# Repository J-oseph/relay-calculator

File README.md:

# relay-calculator
Calculator made from electro-mechanical relays.

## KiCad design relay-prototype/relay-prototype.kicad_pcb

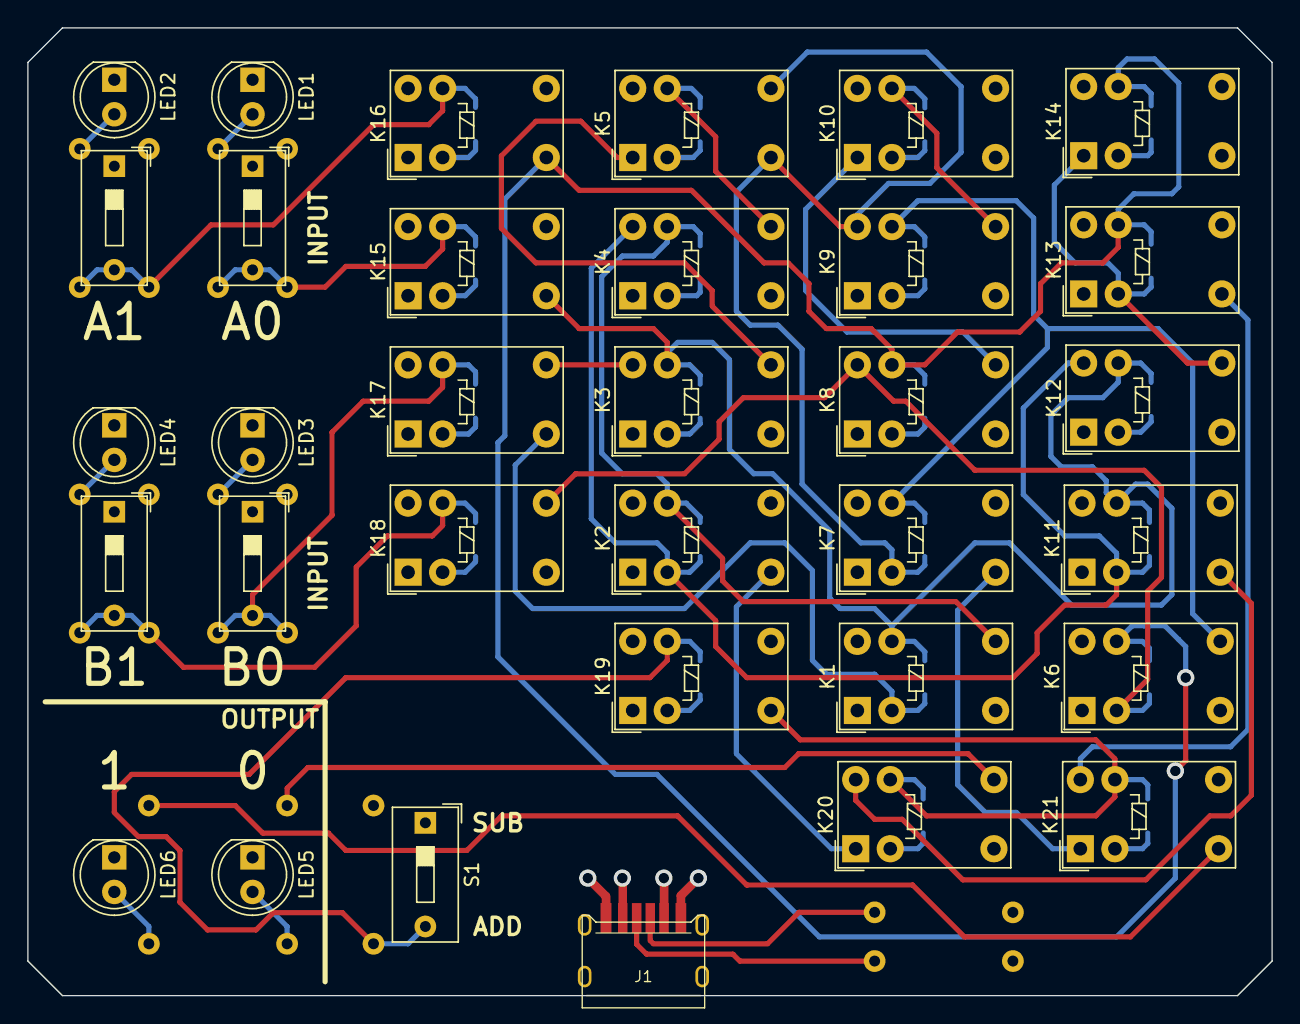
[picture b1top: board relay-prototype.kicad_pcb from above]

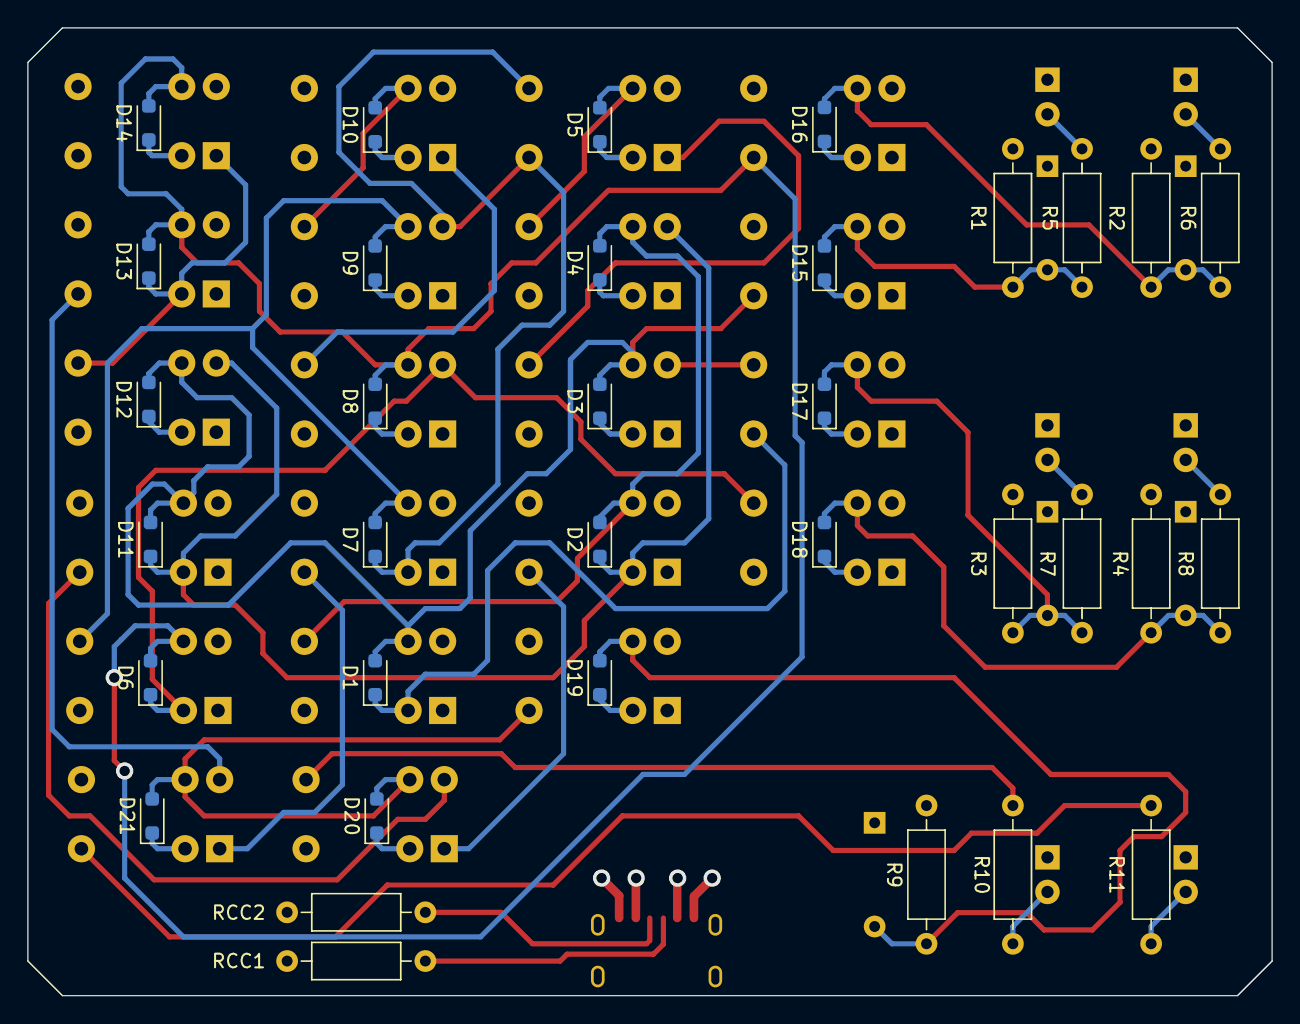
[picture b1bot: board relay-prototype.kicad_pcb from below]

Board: 4 copper layers, 91.4 x 71.1 mm, 67 parts (34 on the bottom side), 37 nets.

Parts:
A0, A1: SW_DIP_x01; SW_DIP_SPSTx01_Slide_9.78x4.72mm_W7.62mm_P2.54mm
B0, B1: SW_DIP_x01; SW_DIP_SPSTx01_Slide_9.78x4.72mm_W7.62mm_P2.54mm
D1, D2, D3, D4, D5, D6, D7, D8, D9, D10, D11, D12, D13, D14, D15, D16, D17, D18, D19, D20, D21: D_TVS; D_SOD-323_HandSoldering
J1: USB_C_Receptacle_PowerOnly_6P; TYPE-C-31-M-17_handsolder
K1, K2, K3, K4, K5, K6, K7, K8, K9, K10, K11, K12, K13, K14, K15, K16, K17, K18, K19, K20, K21: G5V-1; Relay_SPDT_Omron_G5V-1
LED1, LED2, LED3, LED4, LED5, LED6: LED; LED_D5.0mm
R1, R2, R3, R4, R9: 100k; R_Axial_DIN0207_L6.3mm_D2.5mm_P10.16mm_Horizontal
R5, R6, R7, R8, R10, R11: 330; R_Axial_DIN0207_L6.3mm_D2.5mm_P10.16mm_Horizontal
RCC1, RCC2: 5.1K; R_Axial_DIN0207_L6.3mm_D2.5mm_P10.16mm_Horizontal
S1: SW_DIP_x01; SW_DIP_SPSTx01_Slide_9.78x4.72mm_W7.62mm_P2.54mm

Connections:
+5V: A0.1, A1.1, B0.1, B1.1, J1.A9 (VBUS), J1.B9 (VBUS), K1.10, K2.10, K5.10, K6.10, K7.10, K10.10, K11.10, K13.1, K15.10, K16.10, K17.10, K18.10, K19.10, S1.1
A0: D1.2 (A2), D3.2 (A2), D11.2 (A2), D12.2 (A2), K1.9, K3.9, K11.9, K12.9, K15.5, K15.6
A1: D6.2 (A2), D8.2 (A2), D13.2 (A2), D14.2 (A2), K6.9, K8.9, K13.9, K14.9, K16.5, K16.6
ADDCOUT0: D7.1 (A1), K5.5, K5.6, K7.2, K9.10
ADDCOUT1: K10.5, K10.6
B0: D1.1 (A1), K1.2, K3.10, K17.5, K17.6
B1: D6.1 (A1), K6.2, K8.10, K18.5, K18.6
CIN0: D2.1 (A1), D11.1 (A1), K2.2, K4.10, K11.2, K12.10
GND: D3.1 (A1), D4.1 (A1), D5.1 (A1), D8.1 (A1), D9.1 (A1), D10.1 (A1), D12.1 (A1), D14.1 (A1), D15.1 (A1), D16.1 (A1), D17.1 (A1), D18.1 (A1), D19.1 (A1), D20.1 (A1), D21.1 (A1), J1.A12 (GND), J1.B12 (GND), K1.1, K2.1, K3.1, K3.2, K4.1, K4.2, K5.2, K6.1, K7.1, K8.1, K8.2, K9.1, K9.2, K10.2, K11.1, K12.1, K12.2, K13.10, K14.2, K14.10, K15.1, K15.2, K16.1, K16.2, K17.1, K17.2, K18.1, K18.2, K19.1, K19.2, K20.2, K21.2, LED1.1 (K), LED2.1 (K), LED3.1 (K), LED4.1 (K), LED5.1 (K), LED6.1 (K), R1.1, R2.1, R3.1, R4.1, R9.2, RCC1.1, RCC2.1
unnamed: D2.2 (A2), D4.2 (A2), K1.5, K1.6, K2.9, K4.9
unnamed: D5.2 (A2), K4.5, K4.6, K5.9
unnamed: D7.2 (A2), D9.2 (A2), K6.5, K6.6, K7.9, K9.9
unnamed: D10.2 (A2), K9.5, K9.6, K10.9
unnamed: A0.2, D15.2 (A2), K15.9, R1.2, R5.1
unnamed: A1.2, D16.2 (A2), K16.9, R2.2, R6.1
unnamed: B0.2, D17.2 (A2), K17.9, R3.2, R7.1
unnamed: B1.2, D18.2 (A2), K18.9, R4.2, R8.1
unnamed: D19.2 (A2), K19.9, R9.1, S1.2
unnamed: J1.A5 (CC1), RCC1.2
unnamed: J1.B5 (CC2), RCC2.2
unnamed: K3.5, K3.6, K5.1
unnamed: K8.5, K8.6, K10.1
unnamed: LED1.2 (A), R5.2
unnamed: LED2.2 (A), R6.2
unnamed: LED3.2 (A), R7.2
unnamed: LED4.2 (A), R8.2
unnamed: LED5.2 (A), R10.2
unnamed: LED6.2 (A), R11.2
OUT0: K20.5, K20.6, R10.1
OUT1: K21.5, K21.6, R11.1
SELECT: D20.2 (A2), D21.2 (A2), K19.5, K19.6, K20.9, K21.9
SUB0: K11.5, K11.6, K20.10
SUB1: K13.5, K13.6, K21.10
SUBCOUT0: D13.1 (A1), K12.5, K12.6, K13.2, K14.1
SUBCOUT1: K14.5, K14.6
SUM0: K2.5, K2.6, K20.1
SUM1: K7.5, K7.6, K21.1

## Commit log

2023-05-16 moved from sub-dir
2023-05-16 gitignore
2023-05-16 Create LICENSE
2023-05-20 project folder and prototype folder
2023-05-21 schematic for adder, subtractor
2023-05-21 prototype schematic finished for now
2023-05-22 start of pcb, usb-c connector
2023-05-28 prototype board completed, usb 3d model added
2023-06-04 fab outputs, BOM
2023-06-04 prototype schematic pdf
